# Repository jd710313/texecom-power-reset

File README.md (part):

# Texecom Remote Power Reset

> **Project summary:** [`project-summary.html`](project-summary.html): one page with the
> reset timing, fail-safe behaviour, schematic, PCB layers, parts and bench tests.
> [View it rendered](https://htmlpreview.github.io/?https://github.com/jd710313/texecom-power-reset/blob/main/project-summary.html)
> (GitHub shows `.html` files as source), or download the file and open it in a browser.

A single board with an ESP32-C3 (Tasmota) and two on-board relays. It sits
inside a Texecom Premier Elite 64-W housing and can remotely "hard power
reset" the panel by briefly cutting both its battery and 16VAC feeds.

> **Status:** Design rev A with **on-board relays**. Schematic done (ERC clean,
> netlist verified). **PCB rev A routed: DRC clean (0 violations, 0 unconnected)**,
> GND pour on the bottom only, with an **engraved top legend** (`Mill_Legend`).
> Gerbers + drill + legend in `fab/`. Not yet milled or tested.

## Background

The panel occasionally raises an **"AUX 12V output failed"** fault. The only
way to clear it is to remove *all* power (battery and AC) and let the panel
restart. This board lets you do that remotely from Home Assistant.

The root cause (probably an overloaded or tripping AUX output) is being
investigated separately. This board is a remote recovery tool, not a fix.

## Requirements

### Panel

| # | Requirement |
|---|-------------|
| R1 | Panel: **Texecom Premier Elite 64-W** (built-in Ricochet wireless) |
| R2 | Firmware: **V6.05.03LS1** |
| R3 | Panel-side events after a reset (AC/battery fault logs, re-arming, etc.) are **out of scope**. They are handled manually. |
| R4 | AC presence and battery voltage are **already monitored** in Home Assistant through the Texecom integration, so this board doesn't monitor them. |

### Function

| # | Requirement |
|---|-------------|
| F1 | Remotely perform a "hard power reset" of the panel by cutting both the **battery 12V** feed and the **16VAC** feed at the same time. |
| F2 | Off duration: about **3 seconds** (Tasmota `PulseTime 30`). |
| F3 | Controlled from **Home Assistant over WiFi**, and reachable at all times. |
| F4 | The controller must **stay powered** while both panel feeds are cut. |

### Fail-safe

| # | Requirement |
|---|-------------|
| S1 | Panel feeds run through the relays' **NC (normally closed)** contacts. Coils are energised only during a reset, so a dead or unpowered board leaves the panel powered. |
| S2 | **Software timeout:** Tasmota `PulseTime`, so the relays release by themselves even if WiFi drops mid-reset. |
| S3 | **Hardware timeout:** a circuit between each GPIO and relay driver limits the maximum on-time (target about 5–10 s). This covers a firmware hang with the GPIO stuck high, and boot-time GPIO glitches. |

### Power

| # | Requirement |
|---|-------------|
| P1 | Powered from the **12V lead-acid battery only**, about 7.2Ah, tapped *before* the battery relay so it is never switched off. |
| P2 | The whole system is backed by **solar**, so no low-battery cutoff is needed. |
| P3 | Regulator: **Pololu S9V11E2F5** (5V buck-boost, 2–16V in, under 0.2mA quiescent). It supplies 5V to the ESP32-C3 SuperMini (5V pin), the 74HCT4538 and the relay coils. |
| P4 | Regulator input is **16V absolute max**. The battery floats at about 13.7V. The board adds **reverse-polarity protection**, a **bulk input capacitor** (≥33µF; 100µF used) and **transient protection**. |
| P5 | The battery tap on the board gets its **own small fuse** (about 0.5–1A, sized for the board's load). |
| P6 | Low power: Tasmota dynamic `Sleep` (WiFi stays connected). Target about 10–15mA average from the battery. |

### Hardware

| # | Requirement |
|---|-------------|
| H1 | MCU: **ESP32-C3 SuperMini**, socketed on female headers. |
| H2 | Relays: **2 × Songle SRD-05VDC-SL-C on the main PCB** ([Micro Robotics](https://www.robotics.org.za/SRD-5VDC-SL-C)). 5V coil (about 70mA each), contacts 10A at 30VDC / 250VAC, SPDT. Only COM and NC are used. |
| H3 | Each relay has a **transistor driver** (2N2222A), a **flyback diode** (1N4007) and a **red indicator LED** that lights while the coil is energised. |
| H4 | **Single board:** all field wiring lands on the PCB (battery in, battery out to the panel, 16VAC in, 16VAC out to the panel). There is no board-to-board wiring. |
| H5 | Screw terminals: **KF301-2P** (already on hand). 5.0mm pitch, 16A, 250V, 22–14 AWG, side entry, interlocking. Four are used (J1–J4). |
| H6 | **Custom PCB** (KiCad) holding the SuperMini socket, the S9V11E2F5, the 74HCT4538 hardware timeout, the relay drivers, both relays, the battery input protection and fuse, and J1–J4. |
| H7 | Everything must fit **inside the panel housing**. Rev A board is **92 × 70mm**; the relays are the tallest part (about 15.5mm). |
| H8 | The PCB is **CNC-milled in-house**, **double-sided** (FlatCAM with alignment pins, 30° V-bit with 0.1mm tip, 0.7mm tracks proven), from on-hand copper-clad board. There are **no plated through-holes, no solder mask and no silkscreen**. |

## Parts on hand

| Part | Source | Status in this design |
|------|--------|-----------------------|
| ESP32-C3 SuperMini | n/a | U3 |
| KF301-2P screw terminals, 5mm (10-pack) | [Micro Robotics](https://www.robotics.org.za/KF301-2P) | J1–J4. **Suitable:** rated 16A / 250V, against about 1.6A max on the battery path and a 16VAC supply. |
| Capacitor kit (CAPKIT) | [Micro Robotics](https://www.robotics.org.za/CAPKIT) | C1 (100µF), C2/C4/C7/C8 (100nF), C3 (10µF) |
| Female and male headers, heat shrink, bootlace ferrules | n/a | SuperMini socket, Pololu header, wiring |
| REL-2CHAN-335V relay module | [Micro Robotics](https://www.robotics.org.za/REL-2CHAN-335V) | **No longer used** (replaced by on-board relays). Kept as a spare and for bench tests. |

## Wiring concept

```
                  ┌─────────────────────────── Main PCB ───────────────────────────┐
Battery +  ──► J1 BAT IN + ──┬──────────────────────────► K1 COM ─┐  NC            │
                             │                                    └──────► J2 BAT OUT + ──► Panel BATT +
                             └─ F1 → D1 → Pololu 5V → ESP32-C3, 74HCT4538, relay coils │
Battery −  ──► J1 BAT IN − ───── GND ─────────────────────────────────► J2 BAT OUT − ──► Panel BATT −
                                                                                       │
16VAC ~A   ──► J3 AC IN ~A ───────────────────────────► K2 COM ─┐  NC                  │
                                                                └──────► J4 AC OUT ~A ──► Panel AC ~A
16VAC ~B   ──► J3 AC IN ~B ───────────────────────────────────────────► J4 AC OUT ~B ──► Panel AC ~B
                  └────────────────────────────────────────────────────────────────┘
```

Each panel power path passes through **only two screw terminals** (in and out)
and one relay contact.

## Panel facts (Texecom INS176-15 installation manual)

From the *Premier Elite 12-W, 24-W & 48/64-W* sections:

| Item | Value |
|------|-------|
| Battery fuse | **F6, 1.6A electronic PTC** |
| AUX 12V, Digicom, Network 1, Bell/Strobe fuses | 0.9A electronic PTC each |
| Panel current consumption | 150mA |
| Maximum current available | 1.0A, plus 0.3A battery charge (7Ah setting) |
| **Battery kick-start** | "The panel will only become live when the AC Mains is connected or the Battery Kick-start button is pressed." |
| Power-up order | Connect the battery first, then AC. |
| Troubleshooting | "Remove ALL power (AC Mains and Battery) and then reapply", which is the same procedure this board automates. |

**Relay rating check:** each relay path carries at most about 1.6A (the battery PTC
limit) or the panel's AC input current. The SRD-05VDC-SL-C contacts are rated
10A. **OK.**

**Kick-start consequence:** the panel only restarts after a reset if **AC is
present**. A reset during a real AC outage would leave the panel **off** until
someone presses the kick-start button. The Home Assistant script therefore
checks that AC is present before it resets (see below).

---

## Design: rev A (on-board relays)

### Block diagram

```
 Battery + ─J1─┬─ F1 PTC ─ D1 ─┬─ C1/C2/D2 ─ U1 Pololu ─► +5V ─┬─ D3 ─► SuperMini 5V
               │               │  bulk/TVS                   ├─► U2 74HCT4538 VCC
               │               │                             └─► relay coils, LEDs
               └───────────────┼──────────────► K1 COM ─ NC ─► J2 BAT OUT +
                               │
 GPIO4 ─ R9 1k ─┬─ reset ─┐                                          +5V
                └─ RC ────┴─► U2 ch1 (7 s max) ─ Q ─ R7 1k ─► Q1 2N2222A ─► K1 coil ┤ D4 flyback, D6 LED
 GPIO3 ─ R10 1k ─┬─ reset ─┐                                         +5V
                 └─ RC ────┴─► U2 ch2 (7 s max) ─ Q ─ R8 1k ─► Q2 2N2222A ─► K2 coil ┤ D5 flyback, D7 LED

 J3 AC IN ~A ─► K2 COM ─ NC ─► J4 AC OUT ~A        J3 ~B ─► J4 ~B (straight through)
```

### 1. Power input and protection

| Ref | Part | Purpose |
|-----|------|---------|
| J1 | KF301-2P screw terminal | BAT IN (+/−). The power supply taps J1+ on the PCB, **before** the relay path, so it is never switched. |
| F1 | **Resettable PTC fuse**, 1206 SMD, 0.5A hold / 1A trip, 24V (Micro Robotics PTC05A24V) | Protects the board's battery branch (not the panel's battery path). The board draws about 0.25A peak at 12V. After a short, it trips, then resets by itself once the fault is removed. |
| D1 | 1N5822 Schottky (DO-201AD, 3A 40V), in series | Reverse-polarity protection (about 0.3V drop, negligible at about 15mA). |
| C1 | 100µF 35V radial electrolytic | Damps LC spikes from the battery leads, as Pololu recommends for the S9V11 (at least 33µF). |
| C2 | 100nF ceramic (radial, 5.08mm) | High-frequency decoupling. |
| D2 | P6KE18A TVS (DO-15) | Clamps larger transients. Its 15.3V standoff sits above the 13.8V float voltage, so no leakage. It is a last line of protection; C1 is the main LC-spike damper. |
| U1 | **Pololu S9V11E2F5** on a 1×4 header | 5V buck-boost, under 0.2mA quiescent. EN is left open (internal pull-up means always on). |
| C3 | 10µF 50V radial electrolytic | Output decoupling. |
| D3 | 1N5822 Schottky between +5V and SuperMini 5V | **Blocks USB backfeed.** The SuperMini's USB VBUS is tied straight to its 5V pin, so plugging in USB would otherwise push 5V from USB onto the relay coils and the Pololu output. The SuperMini still gets about 4.7V, which is fine for its 3.3V LDO. |

**Current budget (estimated):**

| State | 5V rail | From battery (at 13.6V, about 88% efficiency) |
|-------|---------|------------------------------------------|
| Idle, WiFi connected, Tasmota `Sleep` | about 25–35mA | **about 11–15mA** (0.3Ah/day, solar-backed) |
| Reset (both relays and LEDs on for 3 s) | about 150mA + ESP | about 90mA for 3 s |
| Worst-case peak (WiFi TX + relays) | about 0.5A | about 0.25A |

### 2. Controller: ESP32-C3 SuperMini

- Plugs into **two 1×8 female headers**, so it can be removed for flashing or
  replacement.
- Relay control pins: **GPIO4 → channel 1 (K1, battery)** and **GPIO3 →
  channel 2 (K2, AC)**. (Swapped from the first draft when the SuperMini
  footprint was corrected; this pairing keeps the tracks from crossing.)
  - Neither is a strapping pin (unlike GPIO2, 8 and 9), nor a USB pin (18, 19)
    or the UART0 pin that prints the boot log (GPIO21).
  - Both are plain inputs with **no internal pull-up at reset** (ESP32-C3
    datasheet, Table 2-1), so they can't pulse a relay while the ESP boots.
    GPIO6 (MTCK) and GPIO9 do have a weak pull-up at reset and are avoided.
- R1 and R2: **100k pull-downs** on the 74HCT4538 side of R9/R10. They hold the
  resets low (relays off) while the ESP is booting, unpowered or removed.
- R9 and R10: **1k series resistors** between each GPIO and the 74HCT4538.
  They protect the ESP when the 5V rail is off. See the note in §3.
- The V2 SuperMini's onboard LED is a **WS2812 RGB LED on GPIO8** (a strapping
  pin). It isn't used as a status LED; leave GPIO8 unassigned in Tasmota.
- **Orientation:** the module mounts **component (button) side up** with its
  **USB-C at the right-hand board edge** (engraved "USB →" on the legend), so it
  can be flashed in place. The antenna end therefore points into the board,
  about 8.5mm above the copper on the header sockets. If WiFi is weak inside the
  panel housing (especially a metal one), use the V2's **IPEX external-antenna
  option** (move the small antenna-select link as described on the module's
  info page) and fit the optional U.FL antenna from the BOM (Micro Robotics
  BAT-P60-WIFI-2, a stick-on flexible PCB antenna on a 100mm lead).

### 3. Hardware timeout: 74HCT4538 dual monostable (at 5V)

One chip (**TI CD74HCT4538E**, DIP-16) covers both channels. Each channel behaves as:

> **relay on = GPIO high AND less than T seconds since the GPIO went high**

| GPIO behaviour | Relay |
|----------------|-------|
| Normal 3 s `PulseTime` pulse | On for 3 s (T is longer, so it never cuts a normal pulse short) |
| GPIO stuck **high** (firmware hang mid-reset) | Released after **T about 5–9 s (7 s nominal)**. It cannot re-trigger without a new low-to-high edge. |
| GPIO low or floating (crash, reboot, ESP removed) | Released immediately, because the reset input R is low |
| Short boot glitch high | Only as long as the glitch (µs), so the relay doesn't respond |
| 5V lost | 74HCT4538, drivers and relay coils all unpowered, relay released |

**Why a 74HCT at 5V (not a 74HC at 3.3V):** it runs from the same 5V rail as the
relay drivers, and it gives a full 5V drive to the transistor bases. HCT inputs
use TTL thresholds (**high = 2.0V or above**, low = 0.8V or below), so the ESP's
3.3V GPIO drives them reliably. (It was chosen originally when bench test 1b
showed the relay *module's* input needed 4.77mA; with on-board relays the choice
still stands.)

**Wiring for each channel.** TI pin names are used here; Nexperia's datasheet
swaps the letters A and B, but the **pin numbers and functions are identical**.

| CD74HCT4538 pin (ch1 / ch2) | Connection |
|-----------------------|-----------|
| R 3 / 13 (active-low reset) | Node N: GPIO through **R9/R10 1k**, with **R1/R2 100k** pull-down to GND at the chip side |
| A 4 / 12 (leading-edge / rising trigger) | Node N through **R5/R6 10k**, with **C7/C8 100nF** to GND. The 1ms delay makes sure reset is released **before** the trigger edge arrives. The Schmitt input handles the slow edge. |
| B 5 / 11 (trailing-edge trigger) | Tied to **VCC** (TI: "an unused B should be tied to VCC") |
| CX 1 / 15 | GND |
| RXCX 2 / 14 | REXT **R3/R4 1M** to +5V. CEXT **C5/C6 10µF X5R 1206** to GND through **R11/R12 100Ω** in series (TI's rapid power-down protection, Fig. 13). |
| Q 6 / 10 | Relay driver: **R7/R8 1k** to the Q1/Q2 base (§3a) |
| Q̅ 7 / 9 | Not used |
| VCC 16 | +5V, with **C4 100nF** decoupling |
| GND 8 | GND |

**Timing:** T = 0.7 × REXT × CEXT = 0.7 × 1M × 10µF ≈ **7 s nominal** (TI
datasheet: τ = 0.7·RX·CX, RX min 5k; noise susceptibility "may occur for
RX > 1M", so 1M is the upper limit). It needs to stay above 3.5 s (the longest
`PulseTime`) and, ideally, below 30 s. **Bench test 3** confirms the real value.
Tune it by lowering REXT or changing CEXT. Keep the RXCX traces short.

- **CEXT must be low-leakage.** With REXT at 1M the timing current is only about
  5µA, so an aluminium electrolytic (leakage in the µA range) would upset the
  timing badly. Use an **X7R/X5R ceramic**. Avoid **Y5V** ceramics, which can
  lose 50–80% of their capacitance.
- **Power-down protection:** TI requires protection when CX is 0.5µF or more.
  The 100Ω in series with CX limits the discharge current into pins 2/14 if 5V
  collapses quickly.
- **Use 74HCT4538** (TI CD74HCT4538E from Communica). A 74HC4538 won't reliably
  read 3.3V inputs at 5V, and a CD4538 has too little output drive.

**ESP protection (does 5V reach the ESP?):** no. The ESP pins only drive the
74HCT4538's **inputs**, which are high-impedance CMOS gates. No 5V output
connects to any ESP pin, so the ESP never sees more than its own 3.3V.

The one corner case is the **5V rail being off while the ESP is powered**, for
example on USB for flashing (D3 blocks USB from the 5V rail). If the ESP then
drives a GPIO high, current could flow through the chip's input clamp diode into
the unpowered 5V rail. **R9/R10 (1k)** limit that to under 3mA, which is harmless
for both parts. They cost nothing in normal operation, because the HCT inputs
draw no current.

### 3a. Relay drivers and relays

| Ref (ch1 / ch2) | Part | Purpose |
|-----------------|------|---------|
| R7 / R8 | 1k, 1206 | Base resistor: (5V − 0.75V) / 1k ≈ **4.3mA** base current, within the 74HCT4538's 4mA-class output rating |
| R13 / R14 | 10k, ¼W | Base pull-down: keeps the transistor off if U2 is unpowered or removed from its socket |
| Q1 / Q2 | **2N2222A**, TO-92 | Low-side coil switch. Coil current about 72mA; forced gain about 17, so the transistor is fully saturated. |
| K1 / K2 | **SRD-05VDC-SL-C** | K1 switches the battery (J1 → COM, NC → J2); K2 switches 16VAC ~A (J3 → COM, NC → J4). NO contacts unused. |
| D4 / D5 | **1N4007** | Flyback diode across each coil (cathode to +5V) |
| R15 / R16 + D6 / D7 | 1k, 1206 + **red 3mm LED** | Across each coil: lights (about 3mA) while that relay is energised, that is while the panel feed is **cut** |

**Relay pin-out (KiCad Relay_SPDT_SANYOU_SRD_Series_Form_C, matches the Songle SRD):**
1 = COM, 4 = NC, 3 = NO, 2 and 5 = coil.

**2N2222A pin-out warning:** TO-92 2N2222A parts are usually **E-B-C**, but
some makers use other orders. The footprint is TO-92 inline with pin 1 = E,
2 = B, 3 = C. **Check the pin-out of the actual transistors** before soldering.

**Fail-safe chain:** GPIO low / ESP dead → U2 reset low → Q low → R13/R14 hold
the base low → coil off → **NC closed** → panel powered. U2 unpowered or pulled
from its socket gives the same result.

### 4. Connectors

**Screw terminals:** all **KF301-2P** (5.0mm pitch, 16A / 250V, 22–14 AWG).

| Ref | Label (engraved) | Pin 1 | Pin 2 | Wires to |
|-----|-------------------|-------|-------|----------|
| J1 | BAT IN | + | − | Battery |
| J2 | BAT OUT | + | − | Panel BATT terminals |
| J3 | AC IN | ~A | ~B | 16VAC supply |
| J4 | AC OUT | ~A | ~B | Panel AC terminals |

### 5. Field wiring

| From | To |
|------|-----|
| Battery + / − | J1 BAT IN + / − |
| J2 BAT OUT + / − | Panel BATT + / − (the panel's original battery leads) |
| 16VAC supply ~A / ~B | J3 AC IN ~A / ~B |
| J4 AC OUT ~A / ~B | Panel AC terminals |

**Wire:** 0.5–0.75mm² (20–18 AWG) for the battery and AC runs, with ferrules in
the screw terminals.

**Recommended:** an in-line fuse (about 3A) on the battery + lead, close to
the battery. The battery current now runs through the PCB, and a 7Ah SLA
battery can deliver very high currents into a short before the panel's own F6
PTC (which sits downstream) can do anything.

### 6. PCB

- 2-layer, **about 70 × 50mm** (estimated): two relays (19 × 15.5mm each) in,
  and the relay module, J5, J6, J7 and the control lead out. The housing
  dimensions are still open.
- **Placement:** J1–J4 along one edge with K1/K2 right behind them, so the
  battery and AC paths are short. The SuperMini sits at the opposite edge,
  as far from the relays as possible, with its USB-C at the board edge.
- **Heavy-current traces** (J1 → K1 → J2, J3 → K2 → J4, and the BAT− and AC ~B
  straight-throughs): at least **2mm wide** on 1oz copper (about 3A at
  10°C rise), or copper pours.
- **Clearance:** the 16VAC lines swing about ±23V relative to GND (the
  panel's bridge rectifier references them to 0V). Keep at least 1mm from logic
  traces. This is low voltage, so no mains-level creepage is needed.
- **Footprint pitch:** the KF301 is 5.0mm. Use a 5.0mm footprint (not 5.08mm)
  so that interlocked blocks line up.
- **Through-hole wherever possible:** axial resistors and diodes, radial
  capacitors, TO-92, DIP-16 in a socket, 2.54mm headers. **1206 SMD is
  acceptable** (hand-solderable) and is used for F1, C5/C6 and several resistors.
- GND pour on the **bottom layer only**. The top
  layer carries only tracks, pads and the engraved legend (§6a).
- 2 × M3 mounting holes.

### 6a. CNC-milling rules (H8)

**Process:** KiCad → Gerbers + Excellon drill → **FlatCAM** (isolation and drill
G-code) → CNC. **Double-sided**, with FlatCAM flip alignment using **alignment
pins**. Tool: **30° V-bit, 0.1mm tip**. The machine has milled 0.7mm tracks
reliably (see the example board), and all common drill sizes are available.

Milled boards have **no plated through-holes, no solder mask and no
silkscreen**, so the layout follows these rules:

| Rule | Why |
|------|-----|
| **Double-sided, but a top-layer connection is only allowed on pads that can be soldered on top.** Axial resistors and diodes, and radial capacitors and LEDs mounted slightly raised, can be soldered on top. The IC socket, female headers, male header under the Pololu, relays, TO-92 transistors (usually) and KF301 terminals **cannot**, because their bodies cover the top pads. | There's no plating to carry a top trace to a bottom joint. |
| **Enforced in KiCad:** the footprints of the covered parts get **bottom-copper-only pads**, so neither manual routing nor the autorouter can connect to them on top. | Makes the rule impossible to break by accident, including by the autorouter. |
| **Vias** are drilled and fitted with a **wire link soldered on both sides.** Keep them few (target 10 or fewer), with 0.8mm drill and 2.0mm pads. **0Ω links** (RES-0E-50) can also serve as crossings. | Every via is a manual solder job. |
| **1206 SMD parts go on the bottom side.** | They're soldered on the same side as the through-hole joints. |
| **Traces 0.7mm by default** (proven on this machine; 0.6mm minimum where needed), **clearance at least 0.4mm**. Power paths at least 2mm, and 16VAC traces at least 1mm from logic. | Proven geometry for the 30°/0.1mm V-bit |
| **Oval, oversized pads** (for example 2.0 × 3.0mm for 0.8–1.0mm holes, bigger for terminals, relays and the 1N5822s). | User's standard practice for easy hand soldering |
| **Extra clearance around pads:** a custom KiCad rule of **at least 0.8mm from any pad to other copper** (tracks at 0.4mm to each other), plus **component spacing** that keeps neighbouring pads and bodies well clear. | The user prefers wider isolation around pads for easy hand soldering and no solder bridges. FlatCAM's multi-pass isolation needs room to widen the cut around pads without eating into neighbouring traces. |
| **Drill sizes:** 0.8mm (resistors, small capacitors, LEDs, TO-92, vias), 1.0mm (headers, IC socket, 1N4007, 0Ω links), 1.3–1.5mm (KF301, relay pins, 1N5822 at 1.3mm leads, C1), 3.2mm (M3 mounting holes). | Few tool changes |
| **GND pour on the bottom only.** The top layer has no pour; its unused copper stays as floating copper and carries the engraved legend. | Faster milling and good grounding on the bottom. A top pour would reach pads that can't be soldered on top, and it would leave nowhere to engrave the legend. |
| **SuperMini USB-C at the board edge** (antenna end inward). | Flashing in place, and it let the corrected footprint keep the proven routing. Use the V2's external-antenna option if WiFi is weak. |
| **Legend engraved into the top copper** from the `Mill_Legend` layer (User.1): part outlines, polarity and pin-1 marks, references, the terminal labels BAT IN / BAT OUT / AC IN / AC OUT with + / − on the battery terminals, and a small **ring beside every pad that must be soldered on top** (key: "○ = SOLDER TOP"). The rings are placed so each one is clearly nearest its own pad. Generated so every line stays **at least 0.35mm clear of any top copper feature or hole** (plus half the line width), so an engrave can never cut a track or pad. | No silkscreen. The legend shows where each part goes. |
| After testing, **coat the board** (conformal coat or clear lacquer). | No solder mask, and the board lives in the panel for years. |

**Routing:** I place the parts and then try routing. If that's poor, use the
user's preferred autorouter, the **KiCad routing tools (Go implementation)**, with
the rules above as design rules.

### 6b. KiCad project

| File | Contents |
|------|----------|
| `texecom-power-reset.kicad_pro` / `.kicad_sch` | Project and schematic (A3, single sheet). **Drawn with wires**; only GND, +5V and +5V_MCU use power symbols or labels. |
| `texecom-power-reset-schematic.pdf` | Schematic PDF export |
| `texecom-power-reset.kicad_sym` | Project symbols: ESP32-C3-SuperMini (from the esp32c3-button-led project), Pololu_S9V11E2F5 |
| `texecom-power-reset.pretty/` | Project footprints: ESP32-C3-SuperMini (**pin rows corrected 2026-09-25**: the first version was mirrored, which would have put 5V and GND on GPIO5/GPIO6 with the module button side up), Pololu_S9V11E2x (pin order VOUT, GND, VIN, EN per the Pololu drawing) |
| `backup/` | Earlier schematic versions (label-connected, and wired with the off-board relay module), kept for reference only. **Not** used for the PCB. |
| `project-summary.html` | One-page visual project summary (self-contained HTML, open in a browser) |
| `fab/` | **Reference export** (maintained with the design): Gerbers F.Cu / B.Cu / Edge.Cuts / Mill_Legend, Excellon drill, drill map |
| `kicad-output/` | Working KiCad output folder used for milling (Gerbers, drill and anything else needed) |
| `flatcam/` | FlatCAM work: project files and generated G-code |
| `docs/` | Copper renders (top includes the legend), 3D renders, and the **top and bottom assembly drawings** (`pcb-assembly-top` / `pcb-assembly-bottom`, SVG + PDF) |
| `tools/make_legend.py` | Regenerates the `Mill_Legend` engrave layer, kept clear of all top copper |
| `tools/make_assembly.py` | Regenerates the top and bottom assembly drawings (SVG + PDF) from the board |

**Layout:** power path across the top. **Channel 2** (GPIO3, K2 AC relay) is in
the middle band and **channel 1** (GPIO4, K1 battery relay) in the lower band.
This order avoids wire crossings from the SuperMini. J3/J4 (AC) sit next to K2,
and J2 (BAT OUT) next to K1. The BAT_IN+ wire runs from J1 over the top and down
the right side to K1 COM.

**Reference designators** match BOM.md: U1 Pololu, U2 74HCT4538 (units A/B =
channels 1/2, unit C = power), U3 SuperMini, J1–J4 KF301 terminals, K1/K2
relays, Q1/Q2 2N2222A, F1 PTC, D1/D3 1N5822, D2 P6KE18A, D4/D5 1N4007,
D6/D7 LEDs, C1–C8, R1–R16, MH1/MH2 M3 holes.

**Verification:** ERC 0 errors, 0 warnings. The KiCad netlist was checked net
by net against the intended circuit (32 nets). The only unconnected pins are the
intentional ones (relay NO, Q̅ outputs, Pololu EN, unused SuperMini pins).

### 6c. PCB layout (rev A)

| Item | Value |
|------|-------|
| Board | **92 × 70mm**, 2 layers, 2 × M3 holes (top-left, bottom-right) |
| Placement | Terminals along the bottom edge: **J4 AC OUT, J3 AC IN, J2 BAT OUT, J1 BAT IN** (left to right). K2 (AC) above J4/J3, K1 (battery) above J2/J1. Drivers and LEDs above the relays, 74HCT4538 top-middle, SuperMini top-right (button side up, **USB-C at the right-hand edge**, antenna end pointing inward), power section bottom-right. |
| Routing | KiCad routing tools (drandyhaas), with a milling floor: **0.8mm clearance** everywhere (1.0mm for 16VAC), 0.7mm signal tracks, 1.0mm supply tracks, 2.0mm battery/AC tracks. GND by a **bottom-layer pour only**, plus a few GND tracks. |
| Vias | **16 wire-link vias** (0.8mm drill, 2.0mm pad): solder a short wire on both sides. |
| Legend | `Mill_Legend` layer (User.1), engraved into the top copper with the V-bit. See *Engraving the legend* below. |
| DRC | **0 violations, 0 unconnected** against the project rules (`.kicad_pro` net classes + `.kicad_dru`). |
| Fab files | `fab/`: `texecom-power-reset-F_Cu.gbr`, `-B_Cu.gbr`, `-Edge_Cuts.gbr`, `-Mill_Legend.gbr` (legend engrave), `texecom-power-reset.drl` (Excellon, mm, absolute origin; PTH and NPTH merged), drill map PDF. |

**Drill sizes:**

| Drill | Holes | Used for |
|-------|-------|----------|
| 0.8mm | 66 | Resistors, disc caps, electrolytics, TO-92, DIP socket, the 16 vias |
| 0.9mm | 4 | LEDs |
| 1.0mm | 30 | SuperMini and Pololu headers, 1N4007/P6KE18A, relay coil pins |
| 1.3mm | 14 | KF301 terminals, relay contact pins |
| 1.5mm | 4 | 1N5822 (1.3mm leads) |
| 3.2mm | 2 | M3 mounting holes |

**How the "no top joint on covered pads" rule is enforced** (so the router can't
create a connection that can't be soldered):

- KiCad forces plated pads onto both copper layers, so the covered footprints
  (terminals, relays, DIP socket, headers, TO-92, electrolytics, LEDs) carry a
  **per-pad F.Cu keepout** (no tracks, no vias, no pour) inside the footprint.
  These are in the `*_Mill` footprints in `texecom-power-reset.pretty/`.
- There is **no top pour** at all. The `.kicad_dru` rule **"no top pour on
  covered pads"** (`zone_connection none` on F.Cu) is kept as a guard in case a
  top pour is ever added again. DRC connectivity is therefore honest: every
  connection it counts is solderable.

**Assembly notes for the milled board:**

Two assembly drawings, both printable at 2:1 on A4 landscape (print at 100%).
The vias carry the same numbers on both.

- **Top side** ([PDF](docs/pcb-assembly-top.pdf)): every top-side part with
  its reference and value, its outline with polarity and pin-1 marks, and the
  20 pads that need a top solder joint ringed in orange (the same pads as the
  rings on the engraved legend).
- **Bottom side** ([PDF](docs/pcb-assembly-bottom.pdf)): there's no silkscreen
  on the bottom, so this shows the board as seen from below (mirrored), with the
  eleven 1206 parts labelled and all 16 vias numbered. The through-hole parts
  appear in grey for orientation.

1. **Vias:** fit a wire through each of the 16 vias and solder both sides first.
2. **SMD (1206) parts are on the bottom** (F1, C5, C6, R7–R12, R15, R16): solder
   them first, on the bottom.
3. **Axial parts and disc capacitors** (R1–R6, R13, R14, D1–D5, C2, C4, C7, C8):
   mount them **1–2mm off the board** so the iron can reach the top pads, and
   **solder every pad on both sides**. The holes aren't plated, so the top and
   bottom pads are only joined by solder on the lead. Twenty of these pads carry
   a top track, and for those the top joint is **essential** (some have no
   bottom track at all). They're marked on the board with a small engraved
   **ring (○ = SOLDER TOP)** next to the pad. Soldering the other top pads is
   harmless and keeps the rule simple.

   | Part | Type | Pads with a top track | Net |
   |------|------|-----------------------|-----|
   | R1 | Axial resistor | 1, 2 | U2A reset, GND |
   | R2 | Axial resistor | 1 | U2B reset |
   | R3 | Axial resistor | 1 | +5V |
   | R4 | Axial resistor | 1 | +5V |
   | R5 | Axial resistor | 1, 2 | U2A reset, U2A trigger |
   | R6 | Axial resistor | 1, 2 | U2B reset, U2B trigger |
   | R13 | Axial resistor | none | |
   | R14 | Axial resistor | 2 | GND |
   | D1 | Axial diode (1N5822) | 1 | D1 cathode |
   | D2 | Axial diode (P6KE18A) | 1 | D1 cathode |
   | D3 | Axial diode (1N5822) | none | |
   | D4 | Axial diode (1N4007) | 1, 2 | +5V, D4 anode |
   | D5 | Axial diode (1N4007) | 1 | +5V |
   | C2 | Disc capacitor | 1 | D1 cathode |
   | C4 | Disc capacitor | 1, 2 | +5V, GND |
   | C7 | Disc capacitor | 1 | U2A trigger |
   | C8 | Disc capacitor | 1 | U2B trigger |

   Solder the top joint first, then the bottom. Afterwards, check continuity
   from each ringed pad to the far end of its top track.
4. **Everything else** (terminals, relays, socket, headers, TO-92s, electrolytics,
   LEDs) is soldered on the **bottom only**; their top pads are isolated rings.
   - **SuperMini (U3):** solder male pins to the module and two 1×8 female
     headers to the board (bottom side). Plug the module in **button side up,
     USB-C towards the right-hand board edge**, following the engraved
     "USB →" arrow. Before plugging it in, check that the square pad (pin 1,
     5V) is at the USB end of the row nearest the relays.
5. After testing, coat the board (no solder mask).

**Milling order (double-sided, alignment pins, height map):**

1. **Alignment-pin holes** first, outside the board outline, so the pins are
   ready for the flip.
2. **Bottom side:** probe a height map (no holes yet, so the probe can't drop
   into one), then mill the **B.Cu isolation, mirrored** around the pin axis
   (**4 passes**, see *Isolation passes* below).
3. **Flip** onto the alignment pins and probe a **new height map on the top**
   (the top face isn't flat in the same way as the bottom).
4. **Top isolation** (F.Cu, not mirrored, **4 passes**).
5. **Legend** (Mill_Legend, not mirrored) with the same V-bit, Z zero and
   height map; see below.
6. **Drill from the top** (drill file not mirrored), with a firm sacrificial
   backing so exit burrs on the bottom pads stay small. Re-zero Z after each
   drill change (the height map isn't needed for drilling through). Mill the
   3.2mm M3 holes as circles if you don't have a 3.2mm drill.
7. **Board outline last** (2.4mm tool, 4 passes to −2.0mm, no tabs). The board
   is held on **double-sided tape**, so it stays put after the final pass; tape
   near the edges as well as the middle. The drills go through the tape, so
   clean adhesive off the small bits if holes start to come out ragged.
8. Lightly deburr the bottom pads before soldering.

**Isolation passes (copper layers): use 4, not 1**

The first board was milled with **one pass** of the V-bit (about 0.14mm wide at
−0.07mm). Isolation routing cuts a line **around the outline** of each copper
shape; it doesn't clear the space *between* shapes. With one pass:

- **Top:** there's no pour, so every pad and track sits in unused, floating
  copper only about 0.14mm away. Solder can bridge a pad to that copper, and if
  the same piece touches another pad, you get a short.
- **Bottom:** the Gerber has 0.8mm gaps between tracks, pads and the GND pour.
  One pass traces *both edges* of each gap: narrow gaps get cleared completely
  (the cuts merge), wider or irregular ones (for example around thermal-relief
  spokes) keep a **sliver of copper** between the two cuts. That's why the
  separation looked wide in some places and thin in others.

Settings for both copper layers (FlatCAM Beta, Isolation tool):

| Setting | Value |
|---|---|
| Passes | **4** |
| Overlap | **15–20%** |
| Combine | On (all passes in one job) |
| Tool, depth, height map | Unchanged (30° V-bit, 0.1mm tip, −0.07mm, auto-level) |

That gives about 0.45–0.5mm of isolation from every copper edge: the 0.8mm
bottom gaps are cleared completely (no slivers, even look), and the top pads get
about 0.5mm to the floating copper. The **legend stays a single Follow pass**.
FlatCAM's Non-Copper Clearing would remove all unused copper, but with a 0.1mm
V-bit it's very slow; the extra passes give the clearance that matters.

**Checking a milled board:** under magnification, scrape out any copper slivers
with a sharp hobby knife and brush the dust away. Then check with a continuity
meter for shorts between neighbouring pads, and from each pad to the copper
around it, especially the terminal, relay and 5V pads, before soldering.

**Alignment holes with a 2.4mm fishtail end mill (at 12,000rpm):**

| Setting | Value | Why |
|---|---|---|
| Z (plunge) feed | **100–150mm/min** (no more than about 200) | About 0.0125mm/rev, or 0.006mm per flute on a 2-flute bit: enough to cut chips in FR4. The earlier 60mm/min tends to rub, which heats the resin, glazes the hole and dulls the bit. A fishtail isn't a drill (no point, no self-centring), and hobby machines flex under heavier plunges. |
| Step-down | **1mm per step**, full retract between steps (−1, −2, −3mm) | Clears the fibreglass dust; 3mm total is a 1.6mm board plus about 1.4mm into the spoilboard for the pins. |
| Dust | Vacuum while drilling | Fibreglass dust packs into the flutes. |

- **Pin fit:** a flat-bottomed end-mill hole comes out very close to the bit
  size. If the pins are also 2.4mm, test on scrap first. If they're too tight,
  use a slightly smaller pin, or mill the holes (FlatCAM "mill holes") for a snug
  sliding fit.
- **First hole:** if the bit squeals or the resin turns brown, increase the feed
  a little rather than slowing down.
- These are general carbide-in-FR4 figures for hobby spindles; if the bit's
  supplier lists feeds, use those.

**Hole drills at 12,000rpm (carbide PCB drills in FR4):**

| Drill | Holes | Z (plunge) feed |
|---|---|---|
| 0.8mm | 66 | **60–90mm/min** |
| 1.0mm (includes the 0.9mm LED holes) | 34 | **80–120mm/min** |
| 1.5mm (includes the 1.3mm terminal and relay-contact holes) | 18 | **100–150mm/min** |
| 3.2mm (M3) | 2 | **120–180mm/min** |

- PCB drills are designed for 30,000–100,000rpm. At 12,000rpm each turn must
  take a smaller bite, or thin bits break, so the feed scales with the diameter
  (about 0.005–0.015mm per revolution).
- A single plunge to −2.0mm (no pecking) is fine for a 1.6mm board at these
  sizes. Set **Feedrate Z per tool** in FlatCAM's drilling job and regenerate the
  drill G-code.
- The **0.8mm bit is the fragile one**: keep it at the low end, make sure it
  runs true, and clean tape adhesive off it. On the larger bits, if a bit
  squeals or the hole edges go brown, raise the feed a step rather than slowing
  down.
- These are general figures for hobby spindles; if the drill supplier lists
  feeds, use those.

**Engraving the legend (FlatCAM):**

The legend Gerber is made of 0.15mm-wide lines. Normal isolation routing would
cut *around* each line (a double outline); **Follow** geometry runs the tool
once down the **centre** of each line, so the V-bit cuts a single thin groove.

1. Load `fab/texecom-power-reset-Mill_Legend.gbr` together with the F.Cu
   Gerber. It shares their origin, so it lines up with the top isolation and
   the alignment pins. Apply **exactly the same** offset or double-sided
   move/mirror to the legend as to F.Cu (select both and apply it once).
2. Make the Follow geometry:
   - **FlatCAM Beta (8.99x):** select the legend Gerber, open the **Isolation
     Routing** tool and tick **Follow**. Tool diameter and passes don't matter
     with Follow. Generate: this creates a `…_follow` geometry.
   - **FlatCAM 8.5:** select the legend Gerber; in the Selected tab under
     *Isolation Routing* tick **Follow**, then *Generate Geometry*.
   - Check the result: text, outlines and rings should be single centre
     lines, not pairs of outlines.
3. CNC job on the follow geometry: tool type **V-shape, 0.1mm tip, 30°**,
   **Cut Z about −0.05 to −0.07mm** (just through 35µm copper, giving a line
   about 0.12–0.14mm wide), **multi-depth off**. Use the feeds, speed and
   travel Z from the top isolation job. A deeper cut widens the lines and blurs
   the small text (1.2mm references, 1.5mm terminal labels), so try a short
   test on scrap first.
4. The cut is very shallow, so **use the top height map** (auto-levelling);
   without it, lines fade out on high spots and cut wide on low ones.
5. The legend was generated at least 0.35mm clear of everything on the top
   copper, so even a slightly deep cut only marks floating (unconnected) copper.
   If you change the layout, regenerate it with `tools/make_legend.py` (run with
   KiCad's Python; see the script header) rather than editing it by hand.

FlatCAM menu names differ a little between versions.

### 7. Tasmota configuration

Build: `tasmota32c3.bin` (flash through the SuperMini's USB-C, with the board
unpowered from the battery; D3 isolates USB from the relay rail).

`Configuration → Configure Module` (Generic ESP32-C3):

| GPIO | Function |
|------|----------|
| GPIO4 | Relay 1 (battery, K1) |
| GPIO3 | Relay 2 (AC, K2) |
| GPIO8 | None (WS2812 RGB LED and strapping pin; leave unassigned) |

Console:

```
Backlog PowerOnState 0; PulseTime1 30; PulseTime2 35; Sleep 100; FriendlyName1 Panel Battery Cut; FriendlyName2 Panel AC Cut
```

| Setting | Why |
|---------|-----|
| `PowerOnState 0` | Relays are **always off** after an ESP reboot or power-up. |
| `PulseTime1 30` | Battery cut for 3.0 s. |
| `PulseTime2 35` | AC cut for 3.5 s. Battery comes back first, then AC, which matches the manual's power-up order. The panel goes live when AC returns. |
| `Sleep 100` | Dynamic sleep for lower average current while WiFi stays connected. |

If the SuperMini has trouble holding a WiFi connection (a known issue with some
SuperMini antenna layouts), try `WifiPower 8.5`. On this board the antenna end
points inward over the PCB, so if the signal inside the panel housing is poor,
switch the V2 to its IPEX external antenna.

### 8. Home Assistant script (example)

Entity IDs are placeholders. Adjust them, and the AC-OK condition, to match the
Tasmota and Texecom integrations.

```yaml
script:
  texecom_hard_power_reset:
    alias: "Texecom hard power reset"
    mode: single
    sequence:
      # Never reset without AC: the panel would not restart without the kick-start button.
      - condition: state
        entity_id: binary_sensor.texecom_ac_ok        # placeholder
        state: "on"
      - action: switch.turn_on
        target:
          entity_id:
            - switch.texecom_reset_panel_battery_cut   # placeholder
            - switch.texecom_reset_panel_ac_cut        # placeholder
```

### 9. Bench tests before installing

Do these with a bench supply of about 12–13.8V on J1, **before** connecting
the panel.

1. **Power-up:** the +5V rail reads 4.9–5.2V, both LEDs stay **off**, and both
   relays stay released. The NC contacts show continuity: J1+ to J2+, and
   J3 ~A to J4 ~A.
2. **Normal pulse:** turn on `Power1`. K1 clicks, D6 lights, and J1+ to J2+ opens
   for 3.0 s, then everything releases. Repeat with `Power2` (K2, D7, 3.5 s).
3. **Hardware timeout:** set `PulseTime1 0` (no software timeout) and turn on
   `Power1`, so the GPIO stays high. K1 should release after about 5–9 s
   (7 s nominal) and stay off. Afterwards, restore `PulseTime1 30`. Repeat for
   channel 2.
4. **Fail-safe:** unplug the SuperMini, and separately pull U2 from its
   socket. Both relays must stay released (NC closed) and the LEDs off.
5. **USB isolation:** with J1 disconnected, plug in USB. The relays, LEDs and
   +5V rail must **not** power up.
6. **Idle current:** measure the J1 current with WiFi connected. The
   target is about 15mA or less.

### Bill of materials

The full BOM and sourcing tracker (on hand / Micro Robotics / Communica) is in
**[BOM.md](BOM.md)**.

## Commercial alternative: ESP8266 2 × 30A relay board

If milling the custom board isn't worth it, Micro Robotics'
[ESP8266-2CH-30A](https://www.robotics.org.za/ESP8266-2CH-30A) (R236, 83 × 68mm)
can do the same job with the same wiring (checked against its
[schematic](https://github.com/microrobotics/ESP8266-2CH-30A/blob/main/Schematic_ESP8266-2CH-30A.jpg)):

- **Wiring:** battery + through relay 1 (COM → **NC**), one AC line through
  relay 2 (COM → **NC**); battery − and the other AC line straight to the
  panel. Power the board (7–28V input, LM2596 5V buck) from the battery side
  of relay 1's COM, through the **inline blade fuse** from the BOM, so it's
  never switched off with the panel.
- **Fail-safe:** each relay has an NPN driver with a 1k base resistor and a
  **10k pull-down**, plus a flyback diode and LED. If the ESP crashes, reboots or
  is removed, the relays drop out and the panel keeps its power.
- **Move relay 1 off GPIO16.** The relays reach the ESP through links on header
  P5 (Relay 1 ↔ GPIO16, Relay 2 ↔ GPIO14). GPIO16 goes high briefly at boot,
  which could blip the battery relay on every ESP restart, so wire Relay 1 to
  **GPIO12 or GPIO13** instead (both brought out on P5, no boot glitch).
- **Tasmota** (`tasmota.bin`, Generic module): Relay1 = GPIO12 (or 13),
  Relay2 = GPIO14, Button1 = GPIO0, LedLink_i = GPIO5 (blue LED; check the
  polarity). Use the same `PowerOnState 0; PulseTime1 30; PulseTime2 35`.
  Flash through the UART header with a 3.3V USB-TTL adapter (IO0 to GND while
  flashing); later updates go over the air.

**What it gives up compared with the custom board:**

| | Custom board | ESP8266-2CH-30A |
|---|---|---|
| Hardware timeout (S3) | 74HCT4538 releases the relays after about 7 s even if the firmware hangs with a GPIO high | None. Relies on `PulseTime` and the ESP8266 watchdog (a reset floats the pins and the pull-downs release the relays). A firmware bug that keeps the pin high while the chip keeps running isn't covered. |
| Idle current from the battery | about 11–15mA | about 25–40mA (ESP8266 plus a non-synchronous buck); fine with solar backing |
| Flashing | USB-C, in place | UART header and USB-TTL adapter; OTA afterwards |
| Antenna | Ceramic, plus the V2's IPEX external-antenna option | ESP-12F PCB antenna only (could be weak inside a metal housing) |
| Build effort | Mill, drill and assemble | Buy, move one link, wire up |

Verdict: a sound substitute, especially with relay 1 moved to GPIO12/13. The
custom board is kept for the hardware timeout, lower idle current, USB-C
flashing and the external-antenna option.

## Open items

- [ ] Free space inside the 64-W housing (dimensions still to come), including height for the relays (about 15.5mm)
- [x] ~~Panel fuse ratings~~: the battery fuse is 1.6A PTC, which is well within the 10A relay rating
- [x] ~~Relay module trigger polarity and 3.3V drive (tests 1a/1b)~~: done 2026-09-25 (high-level trigger, 4.77mA at 3.3V). No longer relevant, because the module was replaced by on-board relays.
- [x] ~~KiCad schematic~~: done with on-board relays, drawn with wires, ERC clean, netlist verified (2026-09-25)
- [ ] Check the pin-out of the 2N2222A transistors actually bought (E-B-C expected)
- [x] ~~PCB layout~~: rev A placed and routed, DRC clean, Gerbers and drill in `fab/` (2026-09-25)
- [ ] Mill, assemble and bench-test rev A (section 9)

## Decisions log

| Decision | Reason |
|----------|--------|
| Pololu S9V11E2F5 instead of the XL7015 | The XL7015 (5–80V, 150kHz, non-synchronous) is inefficient at light load and bulky. The S9V11E2F5 has under 0.2mA quiescent current, a light-load mode, and a 10.9 × 16.5mm footprint. |
| Battery-only supply (no 16VAC diode-OR) | Rectified 16VAC peaks at about 22–25V, above the S9V11E2F5's 16V max. Solar backing makes battery drain a non-issue. |
| No low-battery cutoff | The system is solar-backed. |
| No AC or battery monitoring on the board | Already provided by the Texecom integration in HA. |
| KF301-2P terminals (on hand) | Rated 16A / 250V and accepts up to 14 AWG, well above the 1.6A battery path and 16VAC. |
| Hardware timeout in addition to `PulseTime` | `PulseTime` is software and can't release a relay if the firmware hangs with the GPIO high. |
| 4538 monostable for the hardware timeout | One chip covers both channels. Its precise timing (0.7·R·C) beats a MOSFET-threshold RC, and its reset input gives "GPIO AND timer" logic without extra gates. |
| Battery restores 0.5 s before AC (`PulseTime1 30` / `PulseTime2 35`) | Matches the manual's power-up order (battery first, then AC). |
| HA script requires AC present | Without AC the panel won't restart unless the kick-start button is pressed. |
| D3 Schottky diode in the SuperMini 5V feed | The SuperMini's USB VBUS connects straight to its 5V pin. The diode stops USB from backfeeding the relay rail and regulator. |
| Through-hole parts wherever possible; 1206 SMD acceptable | User preference. 1206 is large enough to hand-solder. |
| F1 = PTC05A24V (1206, 0.5A hold) instead of the radial WDS250-500 (0.25A hold) | More margin over the peak load, and it's in stock at Micro Robotics. |
| CEXT 10µF X5R 1206 with REXT 1M | 22µF through-hole ceramics are hard to find. 10µF with 1M gives T ≈ 7 s. |
| 1N5822 for D1/D3 | Micro Robotics stocks the 1N5822, not the 1N5819. |
| Parts sourced from Micro Robotics (robotics.org.za) where possible | User preference. Tracked in BOM.md. The 74HCT4538 and the P6KE18A come from Communica. |
| **74HCT4538E at 5V** instead of 74HC4538 at 3.3V | Bench test 1b measured 4.77mA per relay-module input at 3.3V, too close to a 3.3V 74HC's drive limit. At 5V the HCT has margin, and its TTL input levels still accept 3.3V from the ESP. It also suits the on-board transistor drivers. |
| 1k series resistors (R9/R10) between the GPIOs and the 74HCT4538 | They limit the clamp-diode current if the ESP drives a GPIO high while the 5V rail is off (USB-only power). |
| 100Ω in series with CEXT (R11/R12) | TI's recommended rapid power-down protection for CX of 0.5µF or more, without adding diode leakage across the 1M timing resistor. |
| Kept the Pololu S9V11E2F5 over the on-hand XL4015 and MP4560 modules | XL4015: too large (54 × 23 × 18mm), high idle current, trimpot output. MP4560: acceptable (55V input, pulse skipping), but its trimpot output could drift and over-voltage the ESP, 74HCT4538 and relays. The Pololu has a fixed 5V output and under 0.2mA idle current. |
| Schematic drawn with wires (not only net labels) | Readability. Only GND, +5V and +5V_MCU use power symbols or labels. |
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
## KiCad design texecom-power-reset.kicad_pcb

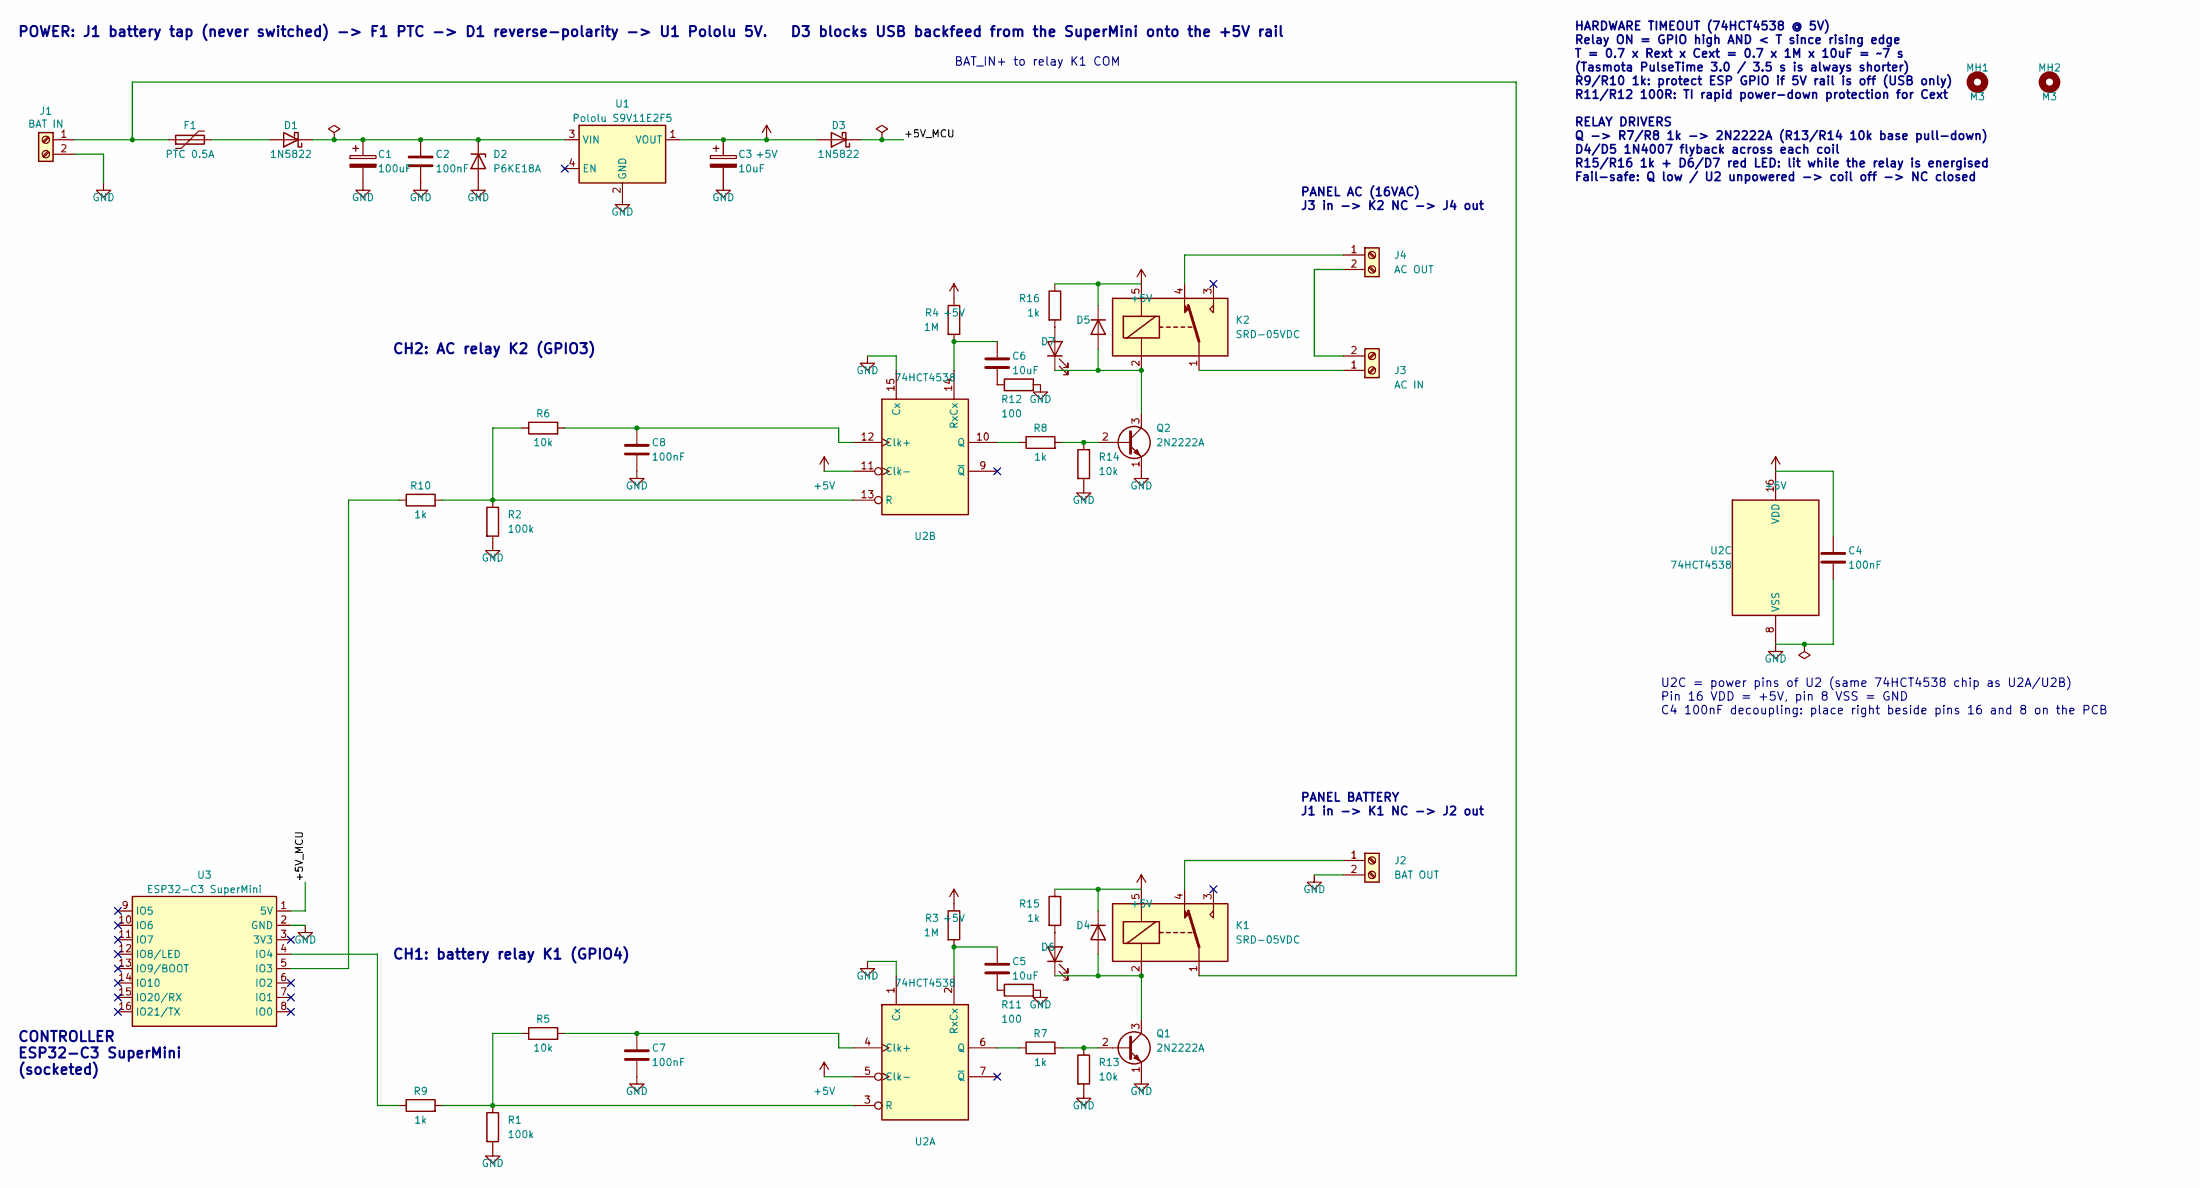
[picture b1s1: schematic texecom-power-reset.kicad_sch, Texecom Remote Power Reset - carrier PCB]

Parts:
C1: 100uF; CP_Radial_D6.3mm_P2.50mm_Mill
C2, C4, C7, C8: 100nF; C_Disc_D5.0mm_W2.5mm_P5.00mm_Mill
C3: 10uF; CP_Radial_D5.0mm_P2.50mm_Mill
C5, C6: 10uF; C_1206_3216Metric_Pad1.33x1.80mm_HandSolder
D1, D3: 1N5822; D_DO-201AD_P15.24mm_Mill
D2: P6KE18A; D_DO-15_P10.16mm_Mill
D4, D5: 1N4007; D_DO-41_P10.16mm_Mill
D6, D7: RED; LED_D3.0mm_Mill
F1: PTC 0.5A; Fuse_1206_3216Metric_Pad1.42x1.75mm_HandSolder
J1: BAT IN; KF301-2P_P5.00mm_Mill
J2: BAT OUT; KF301-2P_P5.00mm_Mill
J3: AC IN; KF301-2P_P5.00mm_Mill
J4: AC OUT; KF301-2P_P5.00mm_Mill
K1, K2: SRD-05VDC; Relay_SRD_Form_C_Mill
MH1, MH2: M3; MountingHole_3.2mm_M3
Q1, Q2: 2N2222A; TO-92_Inline_Wide_Mill
R1, R2: 100k; R_Axial_DIN0207_P10.16mm_Mill
R3, R4: 1M; R_Axial_DIN0207_P10.16mm_Mill
R5, R6, R13, R14: 10k; R_Axial_DIN0207_P10.16mm_Mill
R7, R8, R9, R10, R15, R16: 1k; R_1206_3216Metric_Pad1.30x1.75mm_HandSolder
R11, R12: 100; R_1206_3216Metric_Pad1.30x1.75mm_HandSolder
U1: Pololu S9V11E2F5; Pololu_S9V11E2x_Mill
U2: 74HCT4538; DIP-16_W7.62mm_Socket_Mill
U3: ESP32-C3 SuperMini; ESP32-C3-SuperMini_Mill

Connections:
+5V: C3.1, C4.1, D3.2 (A), D4.1 (K), D5.1 (K), K1.5, K2.5, R3.1, R4.1, R15.1, R16.1, U1.1 (VOUT), U2.5 (Clk-), U2.11 (Clk-), U2.16 (VDD)
+5V_MCU: D3.1 (K), U3.1 (5V)
GND: C1.2, C2.2, C3.2, C4.2, C7.2, C8.2, D2.2 (A), J1.2, J2.2, Q1.1 (E), Q2.1 (E), R1.2, R2.2, R11.2, R12.2, R13.2, R14.2, U1.2 (GND), U2.1 (Cx), U2.8 (VSS), U2.15 (Cx), U3.2 (GND)
unnamed: C5.2, R11.1
unnamed: C6.2, R12.1
unnamed: D1.2 (A), F1.2
unnamed: C1.1, C2.1, D1.1 (K), D2.1 (K), U1.3 (VIN)
unnamed: D4.2 (A), D6.1 (K), K1.2, Q1.3 (C)
unnamed: D5.2 (A), D7.1 (K), K2.2, Q2.3 (C)
unnamed: D6.2 (A), R15.2
unnamed: D7.2 (A), R16.2
unnamed: F1.1, J1.1, K1.1
unnamed: J2.1, K1.4
unnamed: J3.1, K2.1
unnamed: J3.2, J4.2
unnamed: J4.1, K2.4
unnamed: Q1.2 (B), R7.2, R13.1
unnamed: Q2.2 (B), R8.2, R14.1
unnamed: C7.1, R5.2, U2.4 (Clk+)
unnamed: R7.1, U2.6 (Q)
unnamed: R1.1, R5.1, R9.2, U2.3 (R)
unnamed: C5.1, R3.2, U2.2 (RxCx)
unnamed: C8.1, R6.2, U2.12 (Clk+)
unnamed: R8.1, U2.10 (Q)
unnamed: R2.1, R6.1, R10.2, U2.13 (R)
unnamed: C6.1, R4.2, U2.14 (RxCx)
unnamed: R10.1, U3.5 (IO3)
unnamed: R9.1, U3.4 (IO4)

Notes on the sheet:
CH1: battery relay K1 (GPIO4)
POWER: J1 battery tap (never switched) -> F1 PTC -> D1 reverse-polarity -> U1 Pololu 5V. D3 blocks USB backfeed from the SuperMini onto the +5V rail
BAT_IN+ to relay K1 COM
PANEL AC (16VAC) J3 in -> K2 NC -> J4 out
PANEL BATTERY J1 in -> K1 NC -> J2 out
CONTROLLER ESP32-C3 SuperMini (socketed)
CH2: AC relay K2 (GPIO3)
HARDWARE TIMEOUT (74HCT4538 @ 5V) Relay ON = GPIO high AND < T since rising edge T = 0.7 x Rext x Cext = 0.7 x 1M x 10uF = ~7 s (Tasmota PulseTime 3.0 / 3.5 s is always shorter) R9/R10 1k: protect ESP GPIO if 5V rail is off (USB only) R11/R12 100R: TI rapid power-down protection for Cext RELAY DRIV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
U2C = power pins of U2 (same 74HCT4538 chip as U2A/U2B) Pin 16 VDD = +5V, pin 8 VSS = GND C4 100nF decoupling: place right beside pins 16 and 8 on the PCB

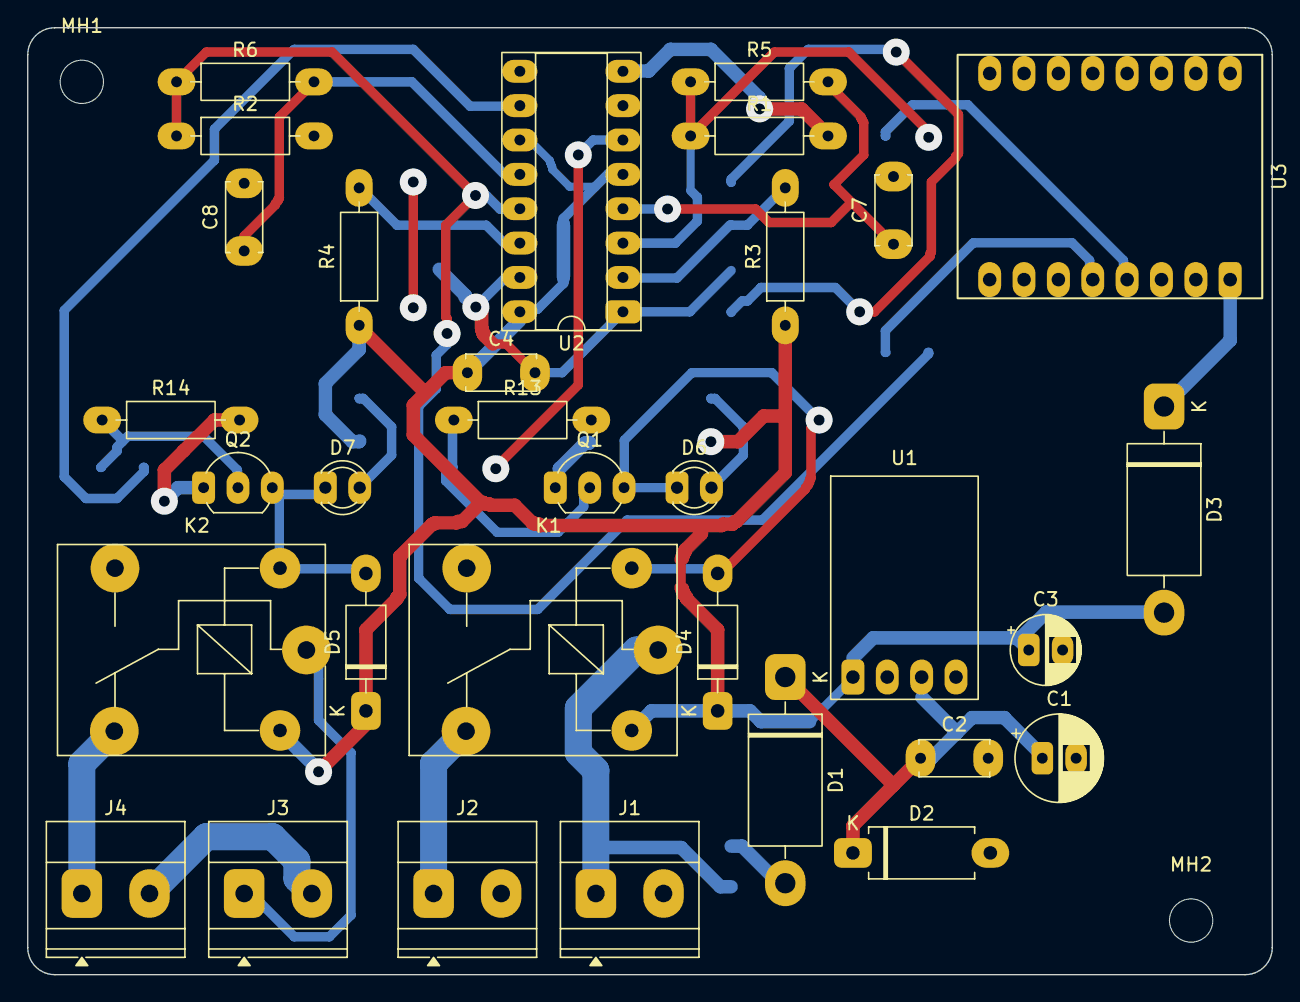
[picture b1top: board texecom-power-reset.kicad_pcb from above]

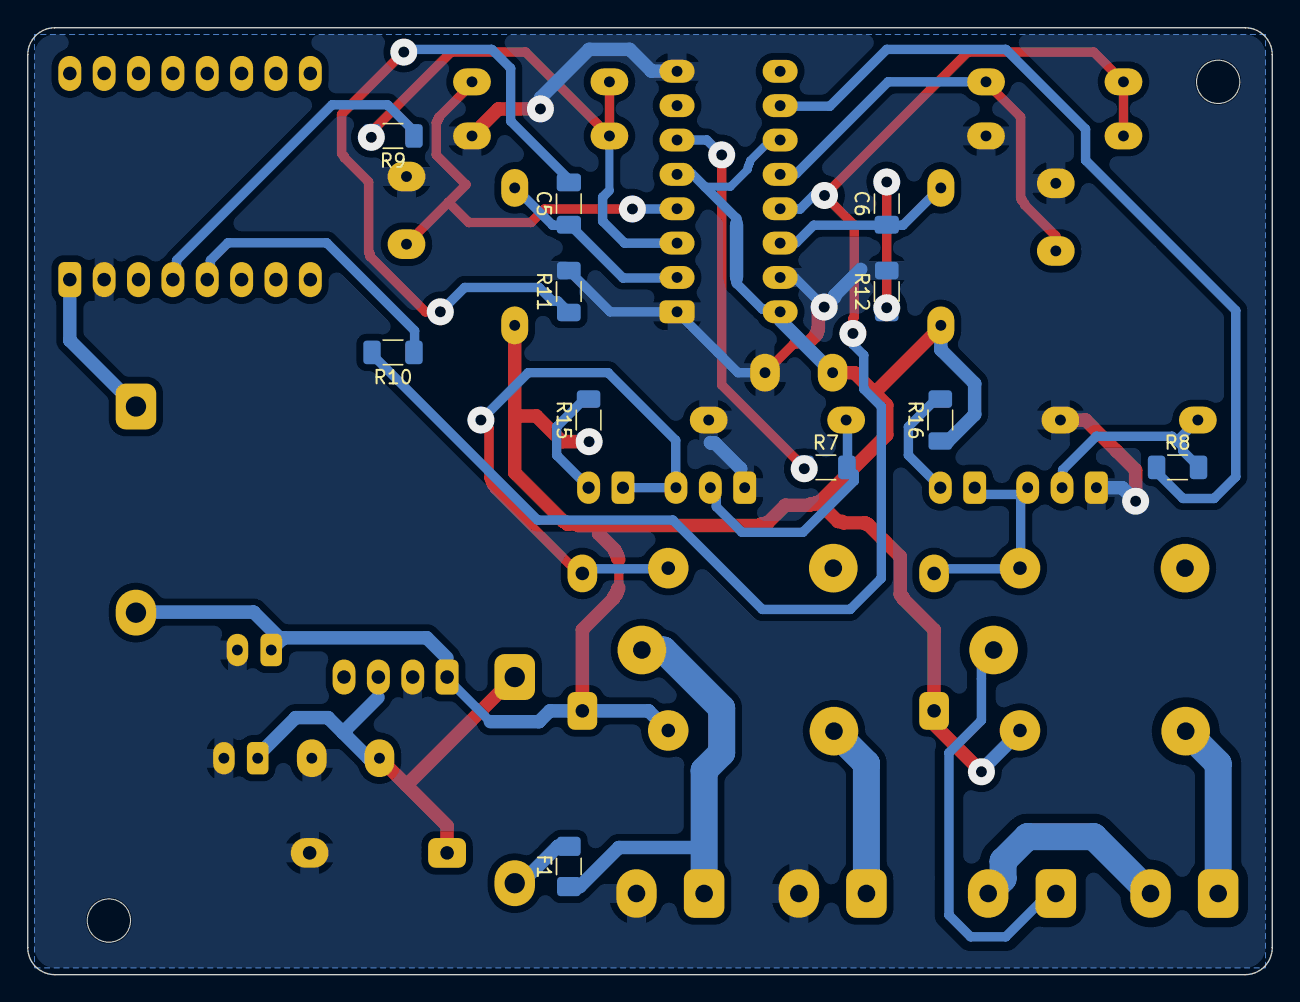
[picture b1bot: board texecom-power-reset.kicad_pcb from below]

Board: 2 copper layers, 92.0 x 70.0 mm, 45 parts (11 on the bottom side), 28 nets.
